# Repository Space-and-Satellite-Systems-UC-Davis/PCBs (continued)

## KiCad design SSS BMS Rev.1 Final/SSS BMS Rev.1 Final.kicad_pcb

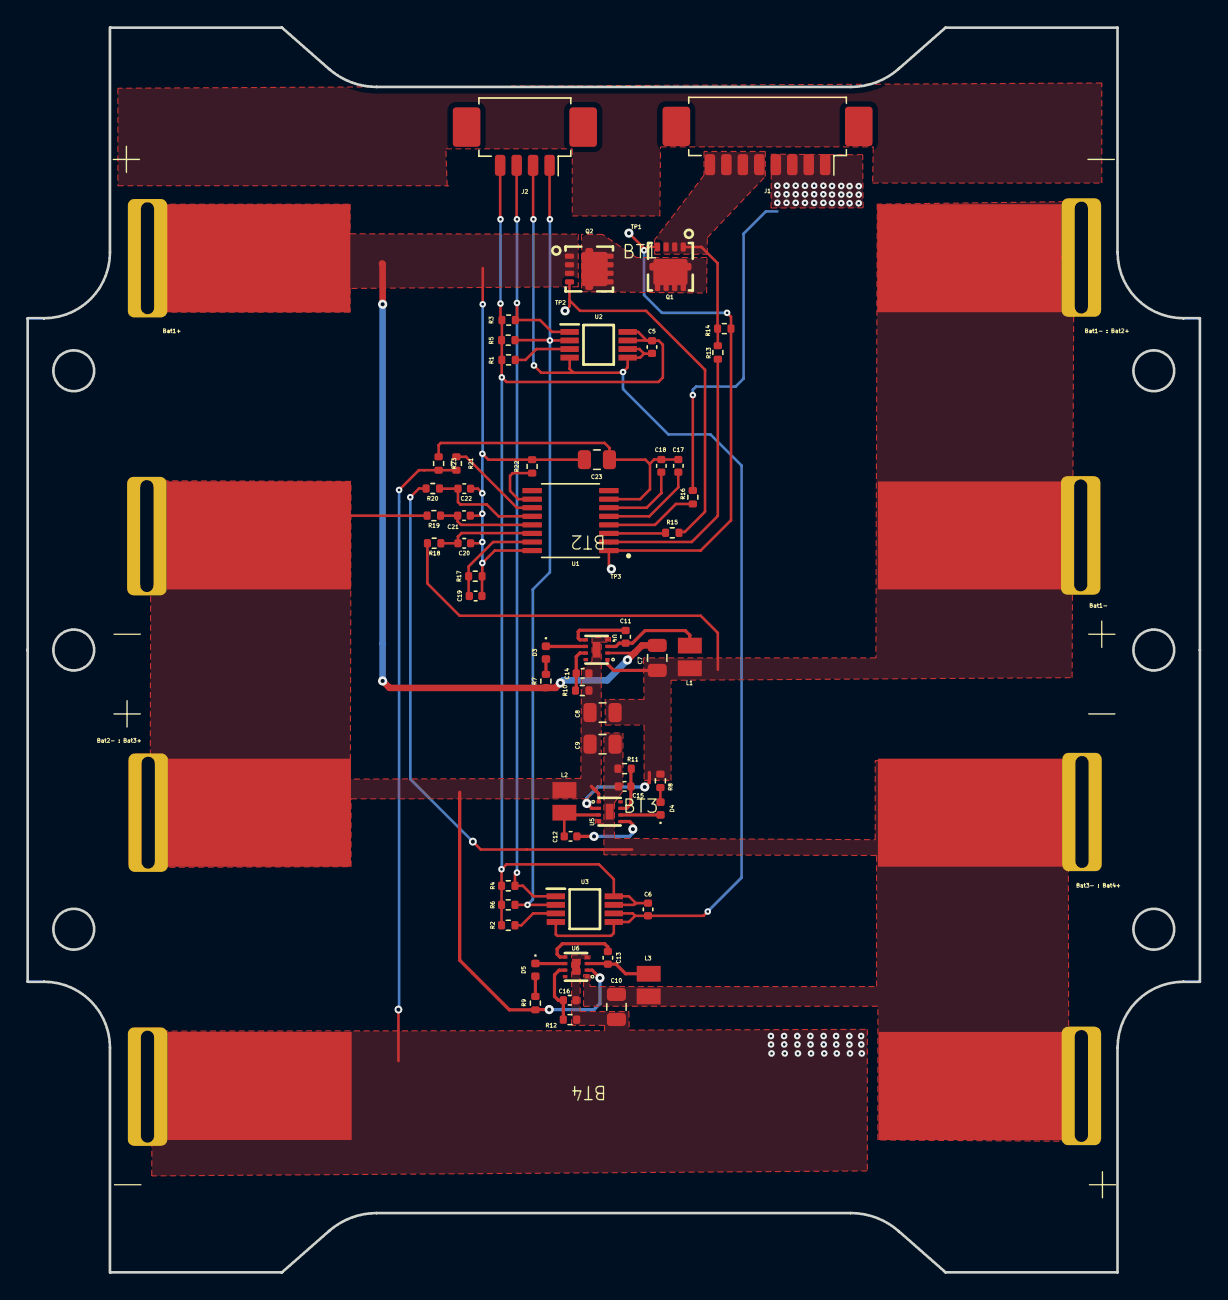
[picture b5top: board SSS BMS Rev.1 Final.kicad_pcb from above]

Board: 2 copper layers, 89.0 x 94.5 mm, 62 parts (0 on the bottom side), 42 nets.

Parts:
BT1, BT2, BT3, BT4: Battery_Cell; bat tabs
C5, C6: 100nF; C_0402_1005Metric
C7, C8, C9, C10, C23: 10uF; C_0805_2012Metric
C11, C12, C13: 10nF; C_0402_1005Metric
C14, C15, C16: 1nF; C_0402_1005Metric
C17, C18, C19, C20, C21, C22: 0.1uF; C_0402_1005Metric
D3, D4, D5: LED; LED_0402_1005Metric
J1: 53261-0871; Molex_PicoBlade_53261-0871_1x08-1MP_P1.25mm_Horizontal
J2: Conn_01x04_Pin; Molex_PicoBlade_53261-0471_1x04-1MP_P1.25mm_Horizontal
L1, L2, L3: 1uH; INDC 2016 X100
Q1, Q2: AONR21321; SSS_0402_PMOS
R1, R2, R3, R4, R5, R6, R13, R15: 4.7k; R_0402_1005Metric
R7, R8, R9: 1.8k; R_0402_1005Metric
R10, R11, R12: 200k; R_0402_1005Metric
R14: 1M; R_0402_1005Metric
R16, R17, R18, R19, R20, R21, R22: 1k; R_0402_1005Metric
R23: 10; R_0402_1005Metric
U1: S-8254A; S-8254A (2)
U2, U3: TMP275; TM275 nw
U4, U5, U6: ETA3000D2I; SSS ETA3000D21

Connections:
/BAT1+: BT1.1 (+), C7.1, C19.1, C20.1, C21.1, C22.1, C23.1, Q2.1 (S), Q2.2 (S), Q2.3 (S), R7.2, R17.2, R22.2, U1.16 (VDD), U4.2 (BATP)
/BAT1-: BT1.2 (-), BT2.1 (+), C7.2, C8.1, L1.1, R8.2, R18.2, U4.1 (BATC), U5.2 (BATP)
/BAT2-: BT2.2 (-), BT3.1 (+), C8.2, C9.1, C14.1, L2.1, R9.2, R10.2, R19.2, U4.4 (BATN), U4.9 (EP), U5.1 (BATC), U6.2 (BATP)
/BAT3-: BT3.2 (-), BT4.1 (+), C9.2, C10.1, C15.1, L3.1, R11.2, R20.2, U5.4 (BATN), U5.9 (EP), U6.1 (BATC)
/PAK+: J1.5, J1.6, J1.7, J1.8, Q1.1 (S), Q1.2 (S), Q1.3 (S), R13.2, R14.2
/PAK-: BT4.2 (-), C10.2, C16.1, J1.1, J1.2, J1.3, J1.4, R12.2, R16.1, R21.2, R23.2, U6.4 (BATN), U6.9 (EP)
/isen_scl: J2.1, R5.1, R6.1, U2.2 (SCL), U3.2 (SCL)
/isen_sda: J2.3, R3.1, R4.1, U2.1 (SDA), U3.1 (SDA)
/vcc: C5.1, C6.1, J2.4, R1.2, R2.2, R3.2, R4.2, R5.2, R6.2, U2.7 (A0), U2.8 (V+), U3.7 (A0), U3.8 (V+)
GND: C5.2, C6.2, J2.2, U2.4 (GND), U2.5 (A2), U2.6 (A1), U3.4 (GND), U3.5 (A2), U3.6 (A1)
unnamed: D3.2 (A), R7.1
unnamed: D3.1 (K), U4.6 (STAT)
unnamed: D4.2 (A), R8.1
unnamed: D4.1 (K), U5.6 (STAT)
unnamed: D5.2 (A), R9.1
unnamed: D5.1 (K), U6.6 (STAT)
unnamed: Q1.5 (D), Q2.5 (D)
unnamed: Q1.4 (G), R14.1, U1.1 (COP)
unnamed: Q2.4 (G), R15.2
unnamed: C18.1, U1.6 (CCT)
unnamed: C17.1, U1.5 (CDT)
unnamed: R21.1, U1.11 (CTL)
unnamed: R15.1, U1.3 (DOP)
unnamed: R22.1, U1.10 (SEL)
unnamed: C19.2, R17.1, U1.15 (VC1)
unnamed: C20.2, R18.1, U1.14 (VC2)
unnamed: C21.2, R19.1, U1.13 (VC3)
unnamed: C22.2, R20.1, U1.12 (VC4)
unnamed: R16.2, U1.4 (VINI)
unnamed: R13.1, U1.2 (VMP)
unnamed: C17.2, C18.2, C23.2, R23.1, U1.7 (VSS)
unnamed: R1.1, U2.3 (ALERT)
unnamed: R2.1, U3.3 (ALERT)
unnamed: C11.1, U4.5 (BIAS)
unnamed: C14.2, R10.1, U4.7 (ISET)
unnamed: C11.2, L1.2, U4.3 (SW)
unnamed: C12.2, U5.5 (BIAS)
unnamed: C15.2, R11.1, U5.7 (ISET)
unnamed: C12.1, L2.2, U5.3 (SW)
unnamed: C13.1, U6.5 (BIAS)
unnamed: C16.2, R12.1, U6.7 (ISET)
unnamed: C13.2, L3.2, U6.3 (SW)

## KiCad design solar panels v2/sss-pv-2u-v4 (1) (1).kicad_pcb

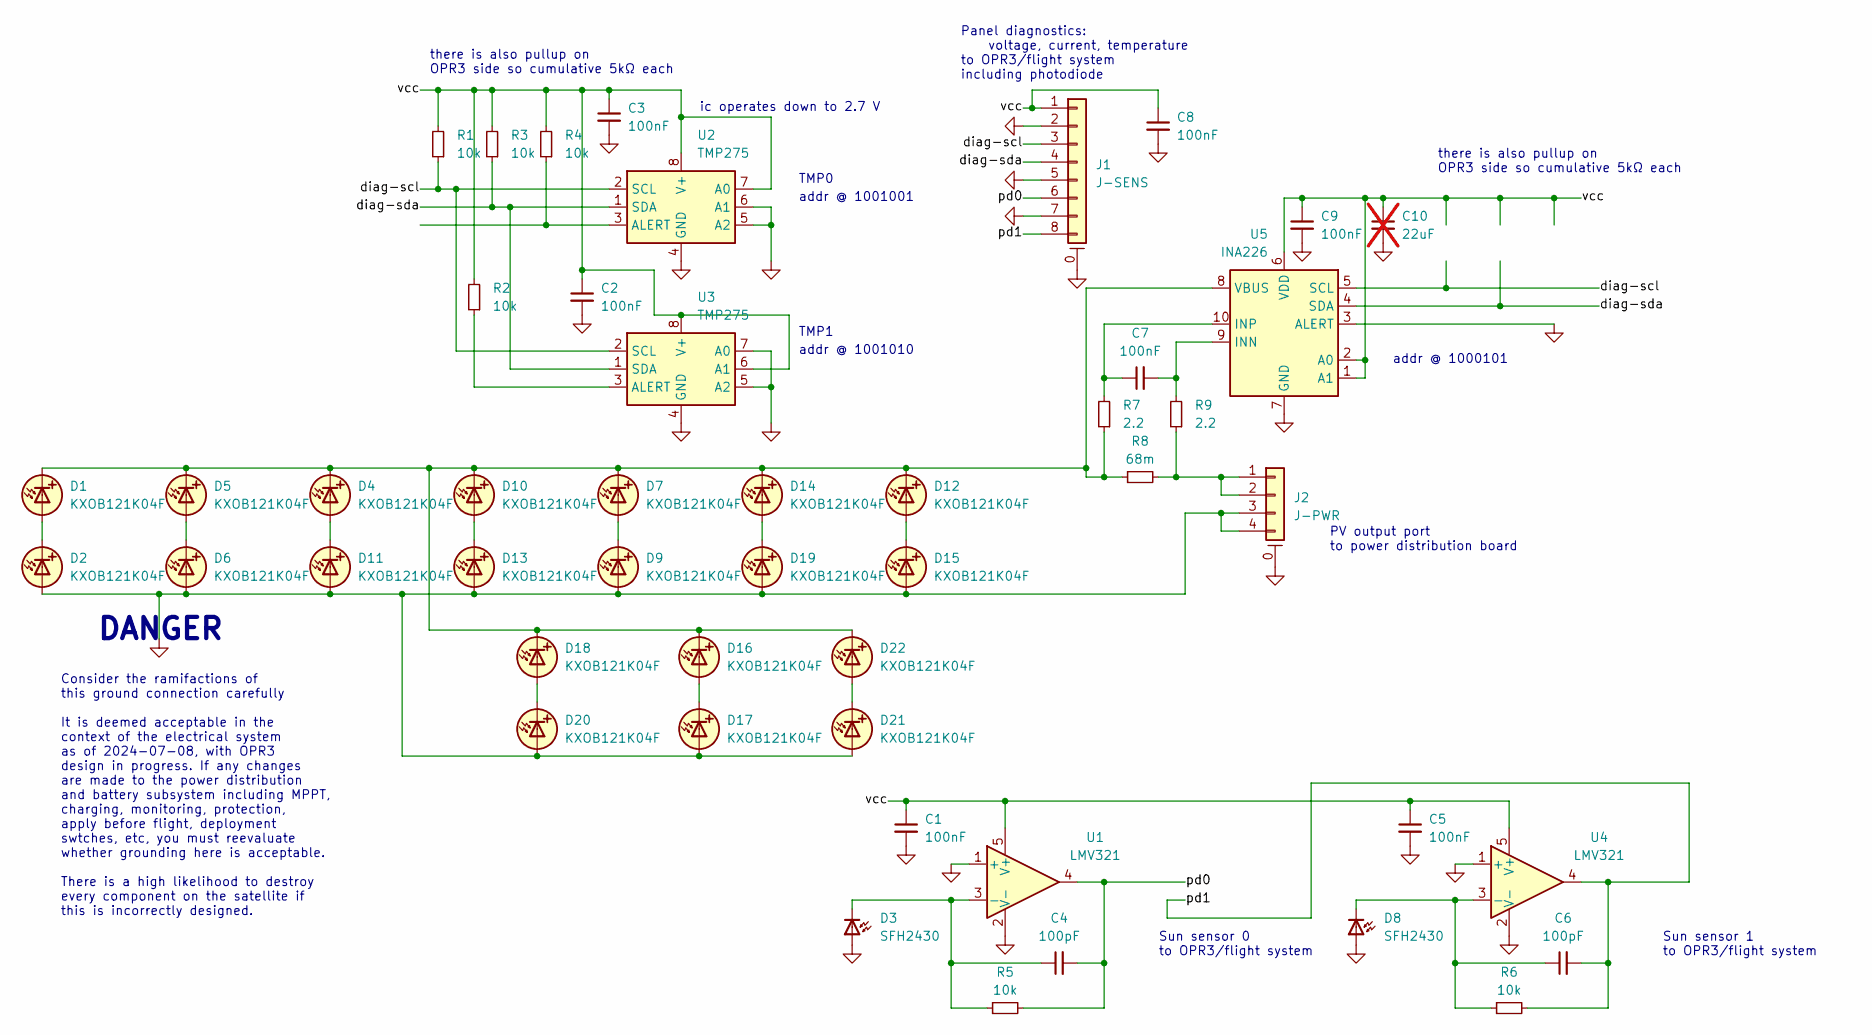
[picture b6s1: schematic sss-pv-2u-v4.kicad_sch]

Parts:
C1, C2, C3, C5, C7, C8, C9: 100nF; Yu-C-0402-mil
C4, C6: 100pF; Yu-C-0402-mil
C10: 22uF; Yu-C-0402-mil; Part CL21A226MAQNNNE; not fitted
D1, D2, D4, D5, D6, D7, D9, D10, D11, D12, D13, D14, D15, D16, D17, D18, D19, D20, D21, D22: KXOB121K04F; Yu-D-PV-KXOB121K04F
D3, D8: SFH2430; Yu-D-PD-Osram-SFH2430
J1: J-SENS; Yu-J-Molex-Picoblade-1x08-SMD-H-532610871
J2: J-PWR; Yu-J-Molex-Picoblade-1x04-SMD-H-532610471
R1, R2, R3, R4, R5, R6: 10k; Yu-R-0402-mil
R7, R9: 2.2; Yu-R-0402-mil
R8: 68m; Yu-R-1206-mil
U1, U4: LMV321; Yu-SOT-23-5
U2, U3: TMP275; Yu-SOP-8-3x3-0.65
U5: INA226; Yu-SOP-10-3x3-0.5

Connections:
/diag-scl: J1.3, R1.1, U2.2 (SCL), U3.2 (SCL), U5.5 (SCL)
/diag-sda: J1.4, R3.1, U2.1 (SDA), U3.1 (SDA), U5.4 (SDA)
/pd0: C4.2, J1.6, R5.2, U1.4
/pd1: C6.2, J1.8, R6.2, U4.4
/vcc: C1.1, C2.1, C3.1, C5.1, C8.1, C9.1, C10.1, J1.1, R1.2, R2.2, R3.2, R4.2, U1.5 (V+), U2.7 (A0), U2.8 (V+), U3.6 (A1), U3.8 (V+), U4.5 (V+), U5.1 (A1), U5.2 (A0), U5.6 (VDD)
GND: C1.2, C2.2, C3.2, C5.2, C8.2, C9.2, C10.2, D2.2 (A), D3.2 (A), D6.2 (A), D8.2 (A), D9.2 (A), D11.2 (A), D13.2 (A), D15.2 (A), D17.2 (A), D19.2 (A), D20.2 (A), D21.2 (A), J1.0 (MountPin), J1.2, J1.5, J1.7, J2.0 (MountPin), J2.3, J2.4, U1.1 (+), U1.2 (V-), U2.4 (GND), U2.5 (A2), U2.6 (A1), U3.4 (GND), U3.5 (A2), U3.7 (A0), U4.1 (+), U4.2 (V-), U5.3 (ALERT), U5.7 (GND)
unnamed: D1.2 (A), D2.1 (K)
unnamed: D1.1 (K), D4.1 (K), D5.1 (K), D7.1 (K), D10.1 (K), D12.1 (K), D14.1 (K), D16.1 (K), D18.1 (K), D22.1 (K), R7.1, R8.1, U5.8 (VBUS)
unnamed: C4.1, D3.1 (K), R5.1, U1.3 (-)
unnamed: D5.2 (A), D6.1 (K)
unnamed: D7.2 (A), D9.1 (K)
unnamed: C6.1, D8.1 (K), R6.1, U4.3 (-)
unnamed: D10.2 (A), D13.1 (K)
unnamed: D4.2 (A), D11.1 (K)
unnamed: D12.2 (A), D15.1 (K)
unnamed: D14.2 (A), D19.1 (K)
unnamed: D16.2 (A), D17.1 (K)
unnamed: D18.2 (A), D20.1 (K)
unnamed: D21.1 (K), D22.2 (A)
unnamed: J2.1, J2.2, R8.2, R9.1
unnamed: R4.1, U2.3 (ALERT)
unnamed: R2.1, U3.3 (ALERT)
unnamed: C7.2, R9.2, U5.9 (INN)
unnamed: C7.1, R7.2, U5.10 (INP)

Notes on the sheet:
Sun sensor 0 to OPR3/flight system
addr @ 1001010
DANGER
TMP0
there is also pullup on OPR3 side so cumulative 5kΩ each
TMP1
PV output port to power distribution board
addr @ 1000101
ic operates down to 2.7 V
Consider the ramifactions of this ground connection carefully It is deemed acceptable in the context of the electrical system as of 2024-07-08, with OPR3 design in progress. If any changes are made to the power distribution and battery subsystem including MPPT, charging, monitoring, protection, app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
Sun sensor 1 to OPR3/flight system
Panel diagnostics: voltage, current, temperature to OPR3/flight system including photodiode
addr @ 1001001

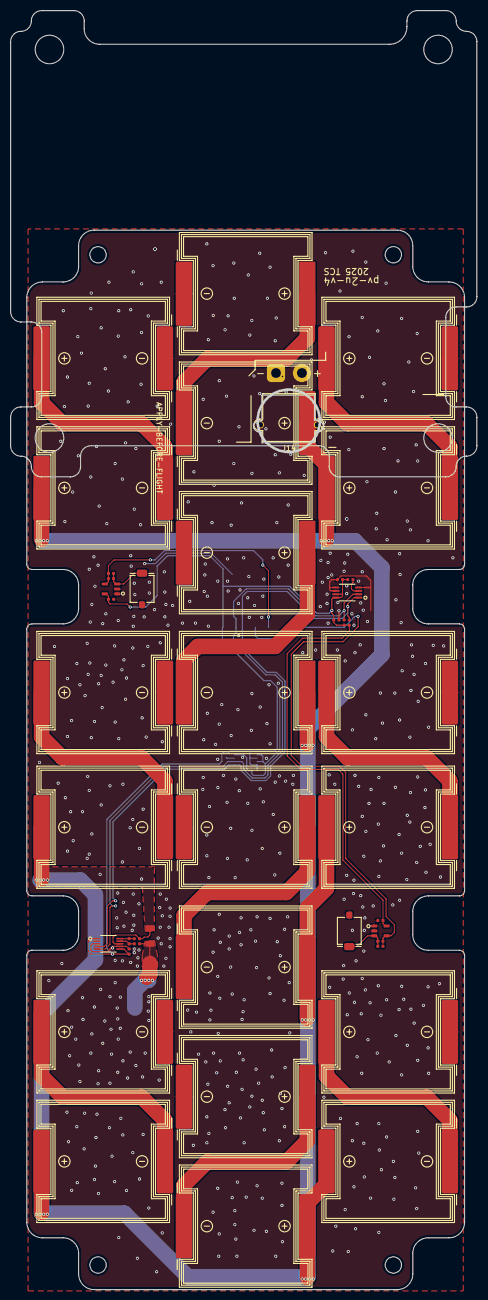
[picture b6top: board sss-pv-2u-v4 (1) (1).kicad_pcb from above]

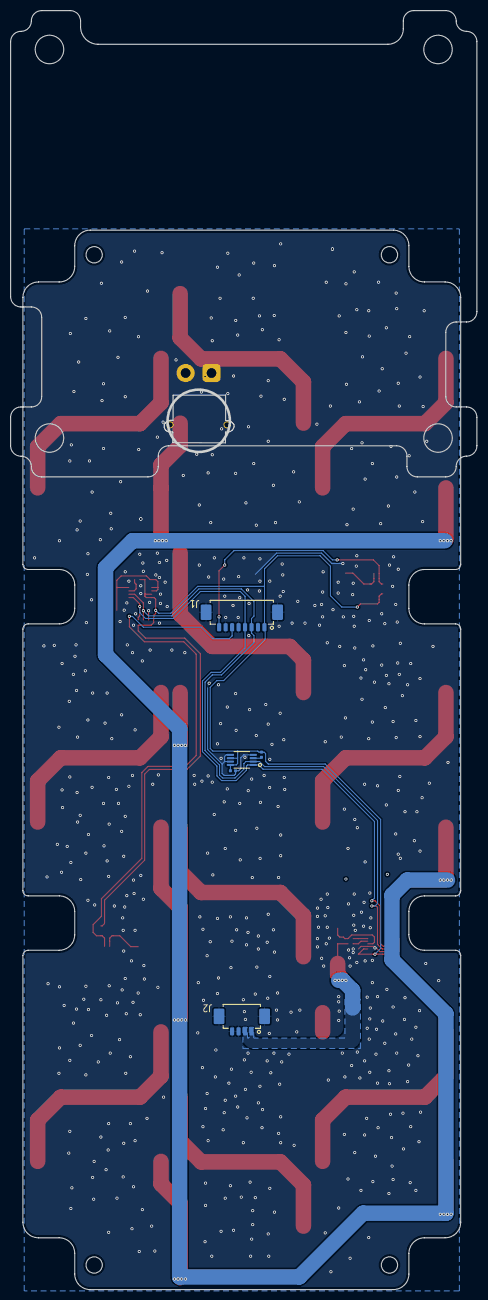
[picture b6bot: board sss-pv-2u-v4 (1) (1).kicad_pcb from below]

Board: 2 copper layers, 90.0 x 246.9 mm, 48 parts (5 on the bottom side), 24 nets.

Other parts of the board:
J14: xt30_2x; AMASS_XT30PW-M_1x02_P2.50mm_Horizontal

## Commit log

2025-09-01 Create BMS PCBs
2025-09-02 OPR3, RF Frontent, and Antenna Board
2025-09-02 OPR3 reference
2025-09-10 Update and rename sss-pv-2u-v4 (1) (1).kicad_pcb to (PCB BAD)sss-pv-2u-v4 (1) (1).kicad_pcb
    This PCB is bad, do not use it. Tim and I will replace it.
    -Aaron
2026-03-28 Create SSS BMS Rev.2 Final
